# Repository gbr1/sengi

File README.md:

# sengi
This repository contains designs for Sengi carrier board.<br>
This board is designed as "developer board" for Erwhi Hedgehog.
<br>

<br>

Other repos:
- [sengi firmware](https://github.com/gbr1/sengi-firmware)
- [sengi ROS node](https://github.com/gbr1/sengi_ros)

<br>
<br>

***Copyright (c) 2019 Giovanni di Dio Bruno under MIT license.***

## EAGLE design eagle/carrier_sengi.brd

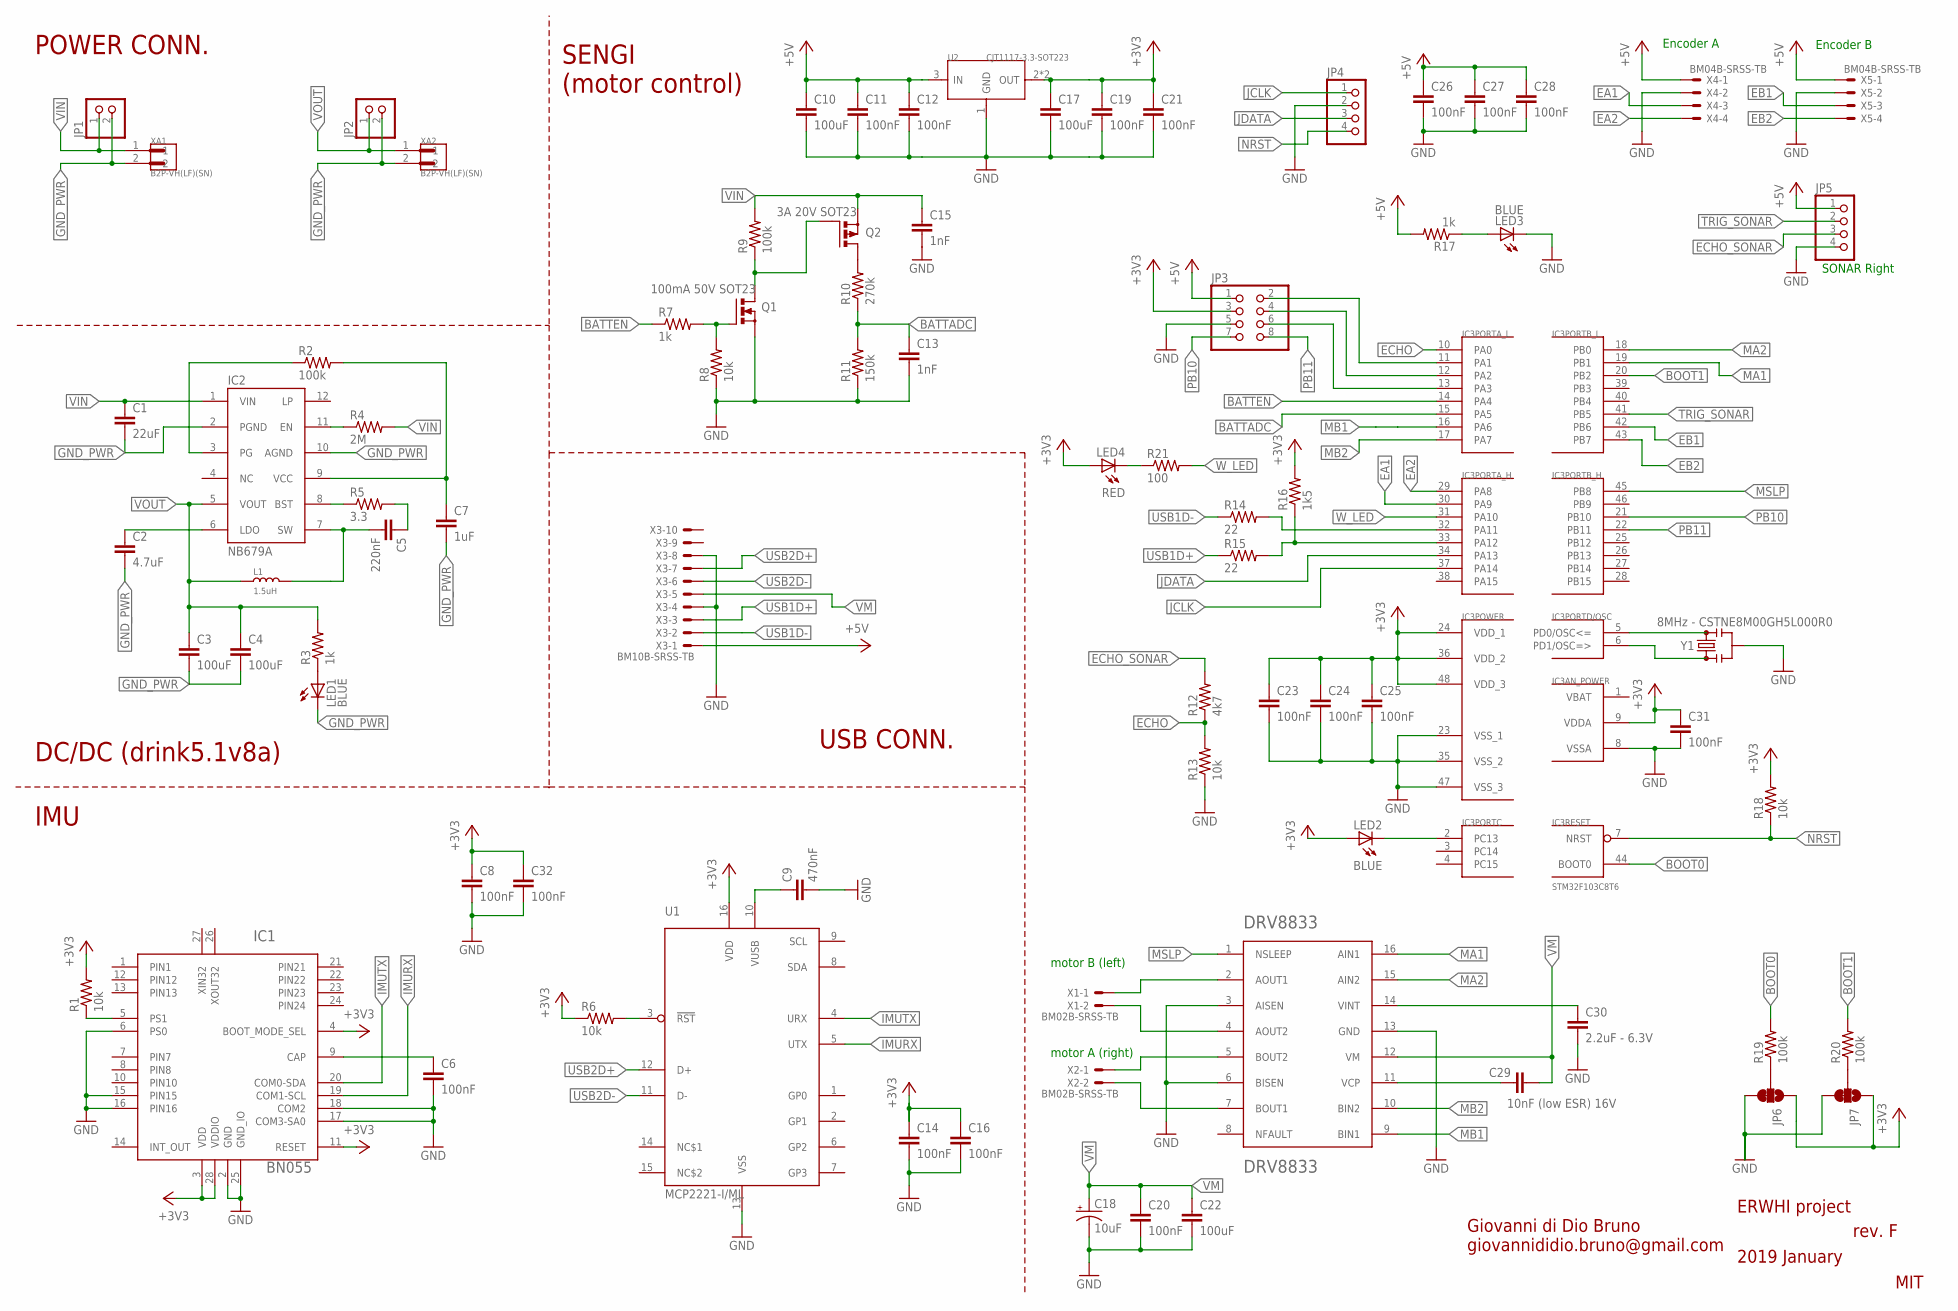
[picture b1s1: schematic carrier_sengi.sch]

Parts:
C1: 22uF; C0805
C2: 4.7uF; C0603
C3, C4: 100uF; C0805
C5: 220nF; C0603
C6, C8, C11, C12, C14, C16, C19, C20, C21, C23, C24, C25, C26, C27, C28, C31, C32: 100nF; C0402
C7: 1uF; C0603
C9: 470nF; C0402
C10, C17, C22: 100uF; C0603
C13, C15: 1nF; C0402
C18: 10uF; EIA3216
C29: 10nF (low ESR) 16V; C0402
C30: 2.2uF - 6.3V; C0402
IC1: BN055; LGA-28_3.80X5.20/0.5
IC2: NB679A; QFN12_2X3
IC3: STM32F103C8T6; TQFP48
IC4: DRV8833PWP; SOP65P640X120-17N
JP1, JP2: PINHD-1X2; 1X02
JP3: PINHD-2X4; 2X04
JP4, JP5: PINHD-1X4; 1X04
JP6, JP7: JUMPER-SMT_3_1-NC_TRACE_NO-SILK; SMT-JUMPER_3_1-NC_TRACE_NO-SILK
L1: 1.5uH; SMD-2P-L6.0XW6.0XH3.0MM
LED1, LED2, LED3: BLUE; CHIP-LED0603
LED4: RED; CHIP-LED0603
Q1: 100mA 50V SOT23; SOT-23
Q2: 3A 20V SOT23; SOT-23
R1, R6, R8, R13, R18: 10k; R0402
R2, R9, R19, R20: 100k; R0402
R3, R7, R17: 1k; R0402
R4: 2M; R0603
R5: 3.3; R0603
R10: 270k; R0402
R11: 150k; R0402
R12: 4k7; R0402
R14, R15: 22; R0402
R16: 1k5; R0402
R21: 100; R0402
U1: MCP2221-I/ML; QFN16-4X4
U2: CJT1117-3.3-SOT223; SOT-223
X1, X2: BM02B-SRSS-TB
X3: BM10B-SRSS-TB
X4, X5: BM04B-SRSS-TB
XA1, XA2: B2P-VH(LF)(SN); JST_B2P-VH(LF)(SN)
Y1: 8MHz - CSTNE8M00GH5L000R0; RESONATOR-SMD-3.2X1.3

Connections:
+3V3: C8.1, C14.1, C16.1, C17.1, C19.1, C21.1, C23.1, C24.1, C25.1, C31.1, C32.1, IC1.3 (VDD), IC1.4 (BOOT_MODE_SEL), IC1.11 (RESET), IC1.28 (VDDIO), IC3.9 (VDDA), IC3.24 (VDD_1), IC3.36 (VDD_2), IC3.48 (VDD_3), JP3.3, JP6.1, JP7.1, LED2.A, LED4.A, R1.2, R6.1, R16.2, R18.2, U1.16 (VDD), U2.2 (OUT), U2.TER (OUT)
+5V: C10.1, C11.1, C12.1, C26.1, C27.1, C28.1, JP3.1, JP5.1, R17.2, U2.3 (IN), X3.1, X4.1, X5.1
BATTADC: C13.1, IC3.15 (PA5), R10.1, R11.2
BATTEN: IC3.14 (PA4), R7.1
BOOT0: IC3.44 (BOOT0), R19.2
BOOT1: IC3.20 (PB2), R20.2
EA1: IC3.30 (PA9), X4.3
EA2: IC3.29 (PA8), X4.4
EB1: IC3.42 (PB6), X5.3
EB2: IC3.43 (PB7), X5.4
ECHO: IC3.10 (PA0), R12.1, R13.2
ECHO_SONAR: JP5.3, R12.2
GND: C6.2, C8.2, C9.2, C10.2, C11.2, C12.2, C13.2, C14.2, C15.2, C16.2, C17.2, C18.-, C19.2, C20.2, C21.2, C22.2, C23.2, C24.2, C25.2, C26.2, C27.2, C28.2, C30.2, C31.2, C32.2, IC1.2 (GND), IC1.6 (PS0), IC1.15 (PIN15), IC1.16 (PIN16), IC1.17 (COM3-SA0), IC1.18 (COM2), IC1.25 (GND_IO), IC3.8 (VSSA), IC3.23 (VSS_1), IC3.35 (VSS_2), IC3.47 (VSS_3), IC4.3 (AISEN), IC4.6 (BISEN), IC4.13 (GND), JP3.5, JP4.2, JP5.4, JP6.3, JP7.3, LED3.C, Q1.P2 (S), R8.1, R11.1, R13.1, U1.13 (VSS), U2.1 (GND), X3.4, X3.8, X4.2, X5.2, Y1.2
GND_PWR: C1.2, C2.2, C3.2, C4.2, C7.2, IC2.2 (PGND), IC2.10 (AGND), JP1.2, JP2.2, LED1.C, XA1.2, XA2.2
IMURX: IC1.19 (COM1-SCL), U1.5 (UTX)
IMUTX: IC1.20 (COM0-SDA), U1.4 (URX)
JCLK: IC3.37 (PA14), JP4.1
JDATA: IC3.34 (PA13), JP4.3
MA1: IC3.19 (PB1), IC4.16 (AIN1)
MA2: IC3.18 (PB0), IC4.15 (AIN2)
MB1: IC3.16 (PA6), IC4.9 (BIN1)
MB2: IC3.17 (PA7), IC4.10 (BIN2)
MSLP: IC3.45 (PB8), IC4.1 (NSLEEP)
unnamed: IC3.5 (PD0/OSC<=), Y1.3
unnamed: IC3.6 (PD1/OSC=>), Y1.1
unnamed: JP6.2, R19.1
unnamed: LED4.C, R21.1
unnamed: IC3.32 (PA11), R14.2
unnamed: IC3.33 (PA12), R15.2, R16.1
unnamed: JP7.2, R20.1
unnamed: IC3.2 (PC13), LED2.C
unnamed: IC4.2 (AOUT1), X1.1
unnamed: IC4.4 (AOUT2), X1.2
unnamed: IC4.5 (BOUT2), X2.1
unnamed: IC4.7 (BOUT1), X2.2
unnamed: C30.1, IC4.14 (VINT)
unnamed: C29.2, IC4.11 (VCP)
unnamed: LED3.A, R17.1
unnamed: IC3.11 (PA1), JP3.2
unnamed: IC3.12 (PA2), JP3.4
unnamed: IC3.13 (PA3), JP3.6
unnamed: C6.1, IC1.9 (CAP)
unnamed: IC1.5 (PS1), R1.1
unnamed: C9.1, U1.10 (VUSB)
unnamed: R6.2, U1.3 (!RST)
unnamed: IC2.11 (EN), R4.1
unnamed: IC2.3 (PG), R2.1
unnamed: C2.1, IC2.6 (LDO)
unnamed: IC2.8 (BST), R5.1
unnamed: C5.1, R5.2
unnamed: C5.2, IC2.7 (SW), L1.2
unnamed: C7.1, IC2.9 (VCC), R2.2
unnamed: LED1.A, R3.1
unnamed: Q1.P1 (G), R7.2, R8.2
unnamed: Q2.P3 (D), R10.2
unnamed: Q1.P3 (D), Q2.P1 (G), R9.1
NRST: IC3.7 (NRST), JP4.4, R18.1
PB10: IC3.21 (PB10), JP3.7
PB11: IC3.22 (PB11), JP3.8
TRIG_SONAR: IC3.41 (PB5), JP5.2
USB1D+: R15.1, X3.3
USB1D-: R14.1, X3.2
USB2D+: U1.12 (D+), X3.7
USB2D-: U1.11 (D-), X3.6
VBAT: IC3.1 (VBAT)
VIN: C1.1, C15.1, IC2.1 (VIN), JP1.1, Q2.P2 (S), R4.2, R9.2, XA1.1
VM: C18.+, C20.1, C22.1, C29.1, IC4.12 (VM), X3.5
VOUT: C3.1, C4.1, IC2.5 (VOUT), JP2.1, L1.1, R3.2, XA2.1
W_LED: IC3.31 (PA10), R21.2

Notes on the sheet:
Encoder A
Encoder B
SONAR Right
motor A (right)
motor B (left)
Giovanni di Dio Bruno giovannididio.bruno@gmail.com
MIT
2019 January
ERWHI project
IMU
DC/DC (drink5.1v8a)
POWER CONN.
USB CONN.
SENGI (motor control)
rev. F

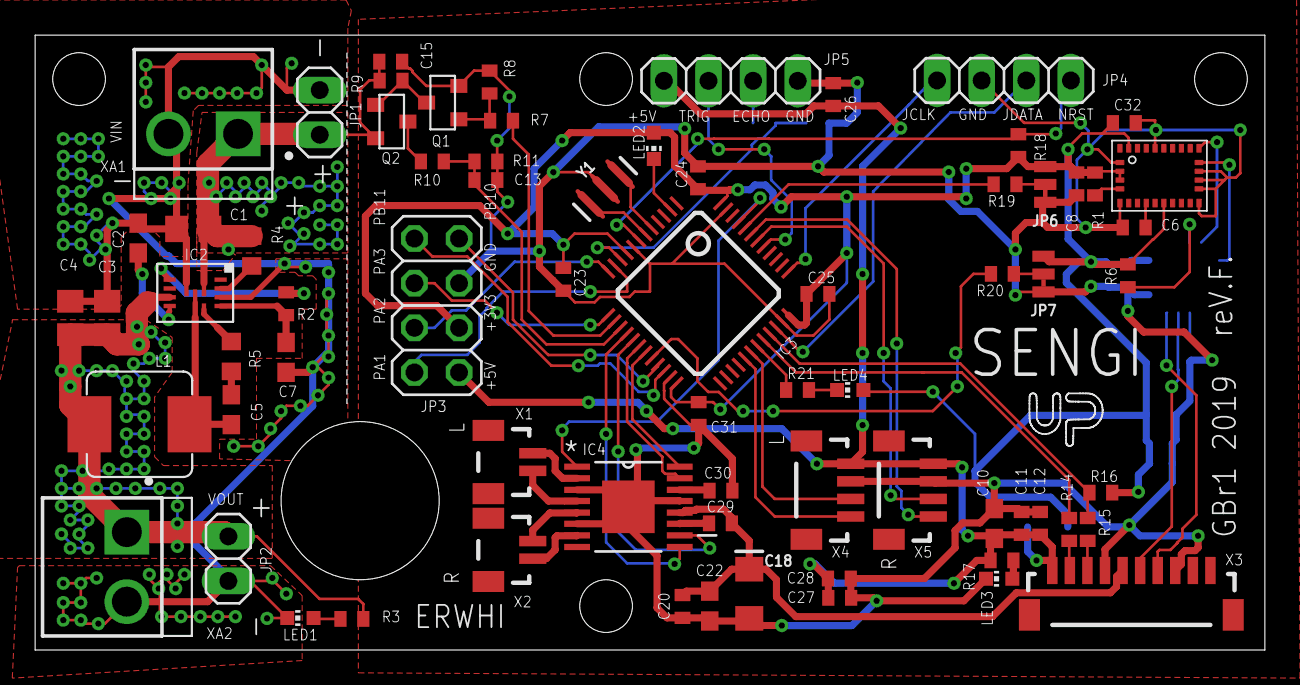
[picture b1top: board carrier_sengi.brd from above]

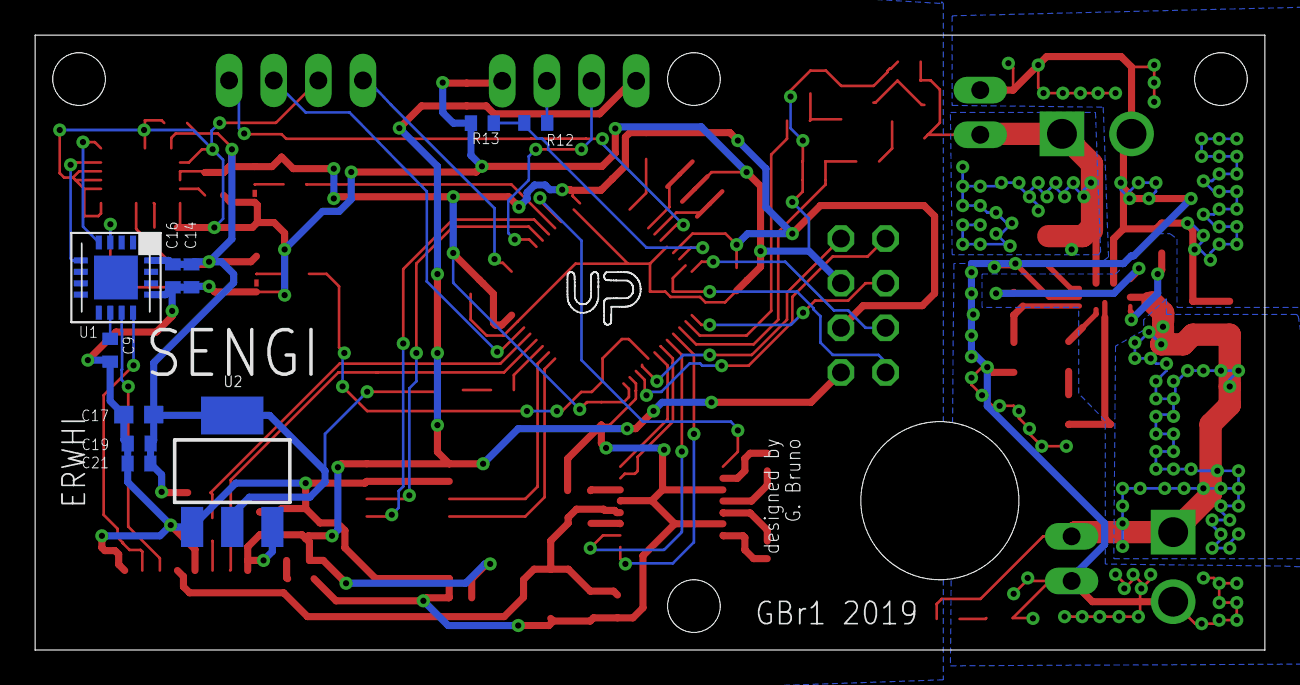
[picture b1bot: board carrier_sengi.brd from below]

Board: 2 copper layers, 70.0 x 35.0 mm, 83 parts (11 on the bottom side), 68 nets.

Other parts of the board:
U$1, U$2: LOGO_UP

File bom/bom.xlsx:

component list
description | ID | pkg | part | qty
22uF | C1 | 0805 | GRT21BR61E226ME13L | 1
4.7uF | C2 | 0603 | CGB3B1X5R1A475K055AC | 1
100uF | C3, C4 | 0805 | GRM21BR60J107ME15L | 2
220nF | C5 | 0603 | GCM188R71E224KA55D | 1
100nF | C6, C8, C11, C12, C14, C16, C19, C20, C21, C23, C24, C25, C26, C27, C28, C31, C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 | 0402 | CL05F104ZO5NNNC | 17
1uF | C7 | 0603 | CL10A105KQ8NNNC | 1
470nF | C9 | 0402 | GRT155C81C474ME01D | 1
100uF | C10, C17, C22 | 0603 | F980J107MMAAXE | 3
10uF | C18 | EIA3216 | TAJA106K006RNJ | 1
10nF | C29 | 0402 | C0402C103K4RECAUTO | 1
2.2uF | C30 | 0402 | GRT155C81C225KE13D | 1
BNO055 | IC1 | LGA 28 | BNO055 | 1
NB679A | IC2 | QFN-12 2x3 | NB679AGD-P | 1
STM32F103C8T6 | IC3 | LQFP48 | STM32F103C8T6 | 1
DRV8833PWP | IC4 | TSSOP16 | DRV8833PWP | 1
1.5uH | L1 | 6x6 | NRS6028T1R5NMGJ | 1
LED BLUE | LED1, LED2, LED3 | 0603 | LTST-C193TBKT-5A | 3
LED RED | LED4 | 0603 | LTST-C190KRKT | 1
BAS40-05-7-F | Q2 | SOT23 | BAS40-05-7-F | 1
10k | R1, R6, R13, R18 | 0402 | RR0510P-103-D | 4
100k | R2, R19, R20 | 0402 | RR0510P-104-D | 3
1k | R3, R17 | 0402 | RR0510P-102-D | 2
2M | R4 | 0603 | RC0402JR-072ML | 1
3.3 | R5 | 0603 | RL0816S-3R3-F | 1
270k | R10 | 0402 | RC0402FR-07270KL | 1
150k | R11 | 0402 | CPF0402B150KE1 | 1
4k7 | R12 | 0402 | RC0402FR-074K7L | 1
22 | R14, R15 | 0402 | RC0402FR-0722RL | 2
1k5 | R16 | 0402 | RC0402FR-071K5L | 1
100 | R21 | 0402 | RR0510P-101-D | 1
MCP2221A | U1 | QFN 4x4 | MCP2221A-I/ML | 1
AZ1117IH-3.3 | U2 | SOT23 | AZ1117IH-3.3TRG1 | 1
BM02B-SRSS-TB | X1, X2 |  | BM02B-SRSS-TB | 2
BM04B-SRSS-TB | X4, X5 |  | BM04B-SRSS-TB | 2
BM10B-SRSS-TB | X3 |  | BM10B-SRSS-TB | 1
B2P-VH(LF)(SN) | XA1, XA2 |  | B2P-VH(LF)(SN) | 2
8MHz | Y1 |  | 8MHz - CSTNE8M00GH5L000R0 | 1

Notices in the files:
parts and their libraries:
SparkFun-Capacitors: Licensing: Creative Commons ShareAlike 4.0 International - https://creativecommons.org/licenses/by-sa/4.0
